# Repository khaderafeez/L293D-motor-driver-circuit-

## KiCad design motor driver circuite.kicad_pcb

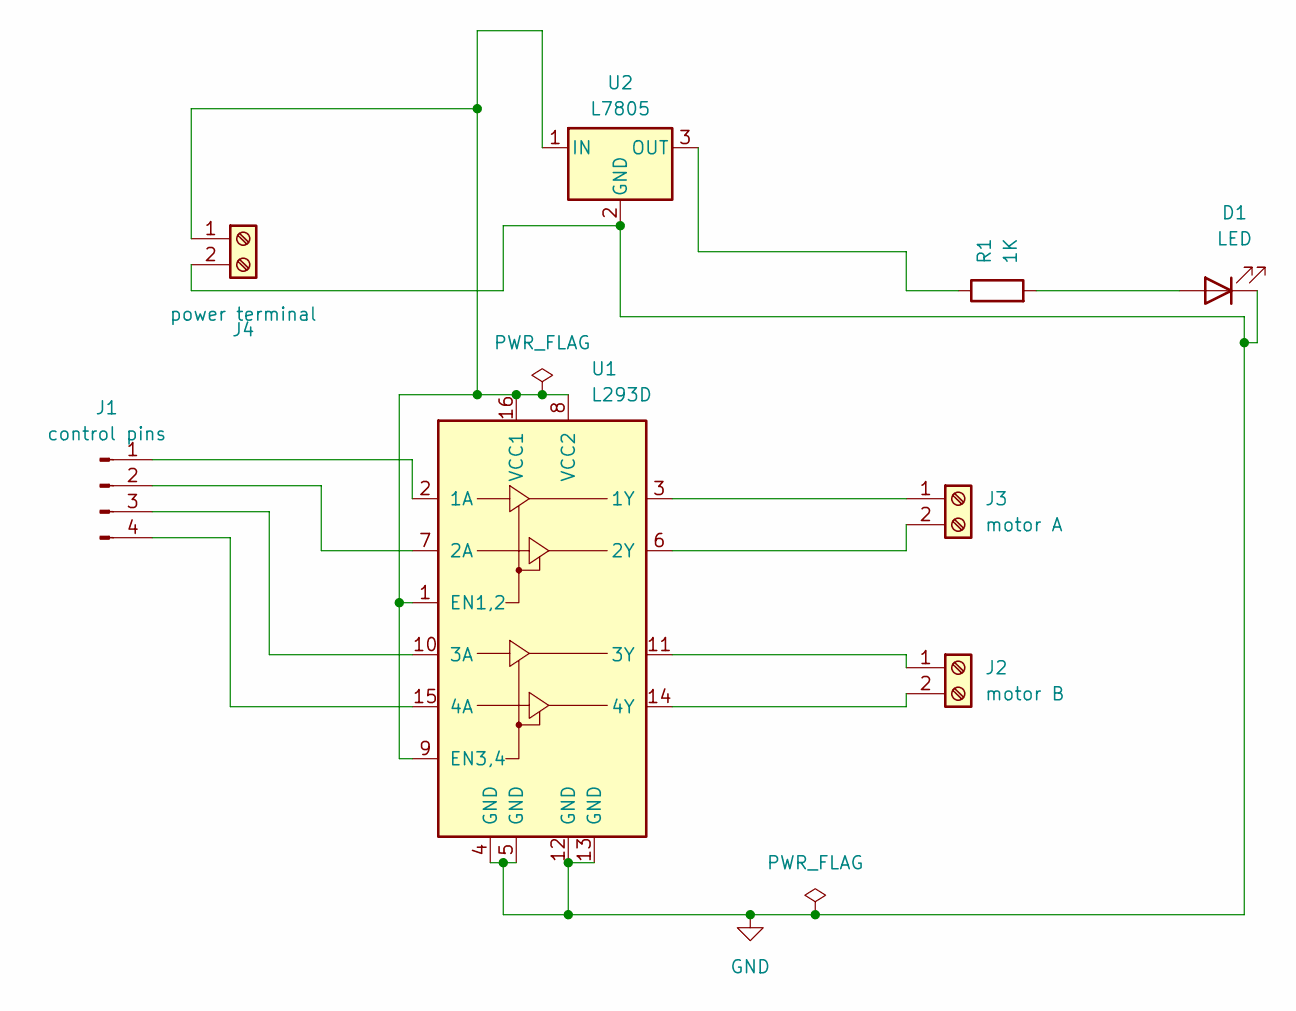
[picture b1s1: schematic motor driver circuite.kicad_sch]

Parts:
D1: LED; LED_D3.0mm
J1: control pins; Pin_D1.0mm_L10.0mm
J2: motor B; TerminalBlock_bornier-2_P5.08mm
J3: motor A; TerminalBlock_bornier-2_P5.08mm
J4: power terminal; TerminalBlock_bornier-2_P5.08mm
R1: 1K; R_Axial_DIN0309_L9.0mm_D3.2mm_P12.70mm_Horizontal
U1: L293D; DIP-16_W7.62mm
U2: L7805; TerminalBlock_bornier-3_P5.08mm

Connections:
GND: D1.1 (K), J4.2, U1.4 (GND), U1.5 (GND), U1.12 (GND), U1.13 (GND), U2.2 (GND)
unnamed: D1.2 (A), R1.2
unnamed: J1.1, U1.2 (1A)
unnamed: J1.2, U1.7 (2A)
unnamed: J1.3, U1.10 (3A)
unnamed: J1.4, U1.15 (4A)
unnamed: J2.1, U1.11 (3Y)
unnamed: J2.2, U1.14 (4Y)
unnamed: J3.1, U1.3 (1Y)
unnamed: J3.2, U1.6 (2Y)
unnamed: J4.1, U1.1 (EN1,2), U1.8 (VCC2), U1.9 (EN3,4), U1.16 (VCC1), U2.1 (IN)
unnamed: R1.1, U2.3 (OUT)

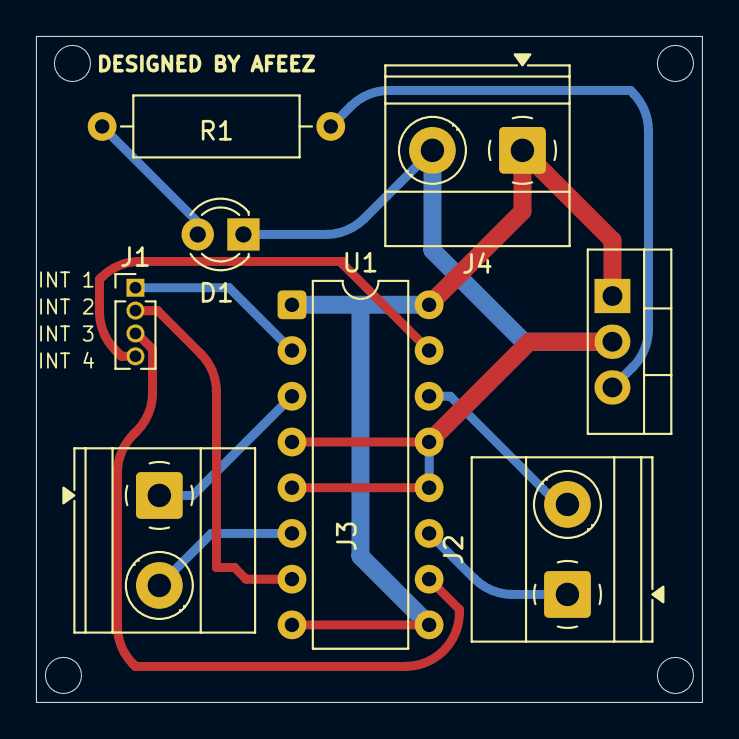
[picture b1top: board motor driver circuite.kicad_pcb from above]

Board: 2 copper layers, 37.0 x 37.0 mm, 8 parts (0 on the bottom side), 12 nets.

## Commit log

2025-04-27 this is intial setup
2025-04-28 this is full tht version of motor driver circuite
2025-04-28 Create README.md
    added markdown file
